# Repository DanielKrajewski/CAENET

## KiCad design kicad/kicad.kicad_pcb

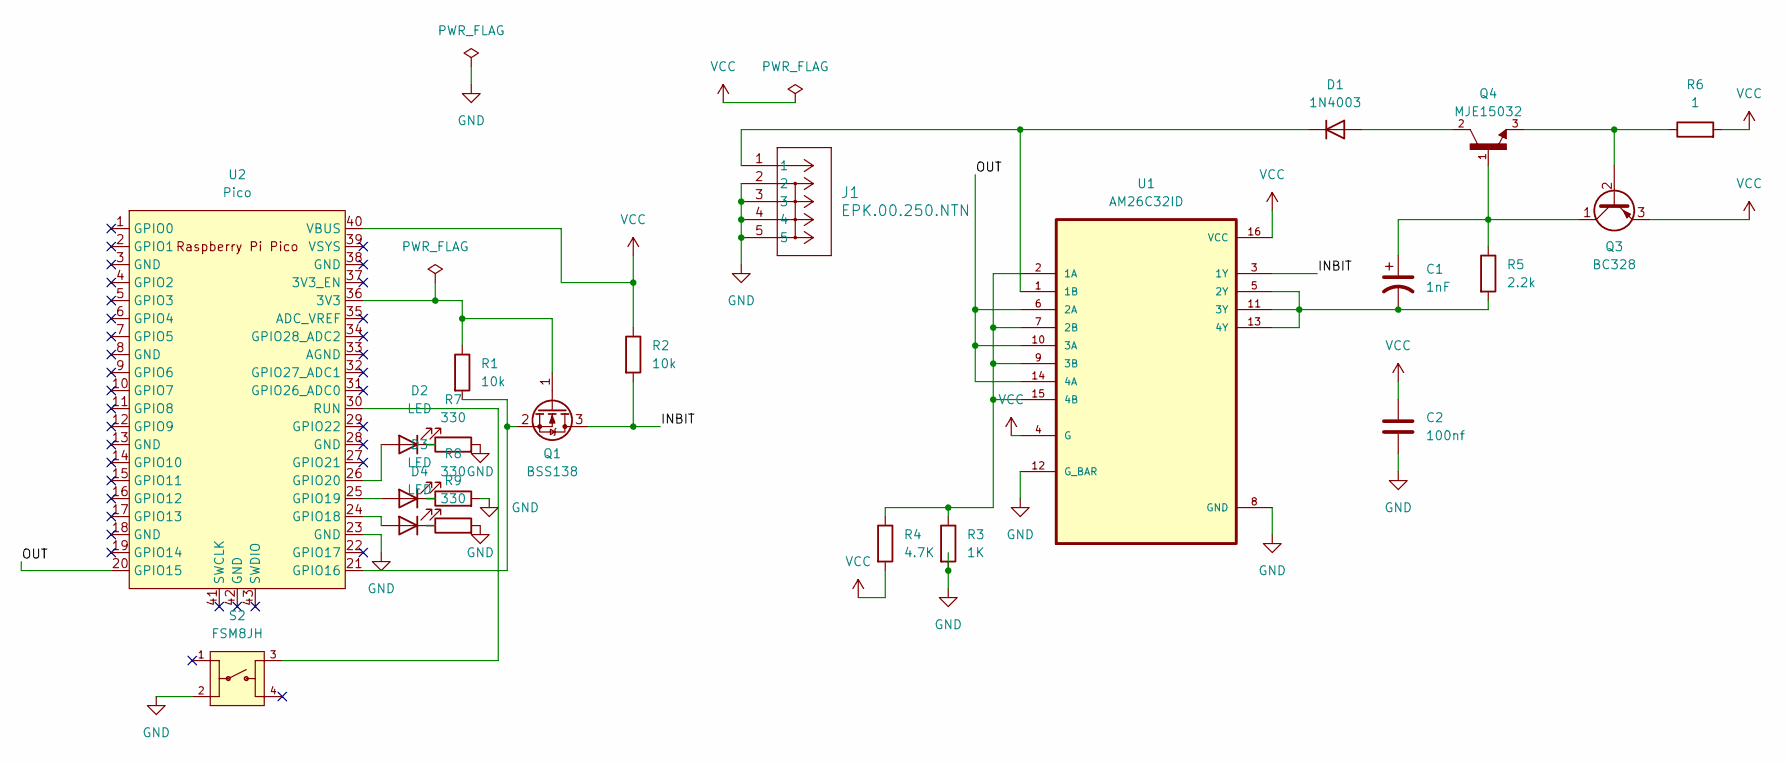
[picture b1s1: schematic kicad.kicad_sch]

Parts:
C1: 1nF; C_0603_1608Metric_Pad1.08x0.95mm_HandSolder
C2: 100nf; C_0603_1608Metric_Pad1.08x0.95mm_HandSolder
D1: 1N4003; D_DO-41_SOD81_P10.16mm_Horizontal
D2, D3, D4: LED; LED_D3.0mm
J1: EPK.00.250.NTN; CONN_EPK.00.250.NTN_LMO
Q1: BSS138; SOT-23
Q3: BC328; TO-92_Inline
Q4: MJE15032; TO-92_Inline
R1, R2: 10k; R_0603_1608Metric_Pad0.98x0.95mm_HandSolder
R3: 1K; R_0603_1608Metric_Pad0.98x0.95mm_HandSolder
R4: 4.7K; R_0603_1608Metric_Pad0.98x0.95mm_HandSolder
R5: 2.2k; R_0603_1608Metric_Pad0.98x0.95mm_HandSolder
R6: 1; R_Axial_DIN0309_L9.0mm_D3.2mm_P12.70mm_Horizontal
R7, R8, R9: 330; R_0603_1608Metric_Pad0.98x0.95mm_HandSolder
S2: FSM8JH; SW_FSM8JH; PARTREV C10
U1: AM26C32ID; SOIC127P600X175-16N
U2: Pico; RPi_Pico_SMD_TH

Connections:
/INBIT: Q1.3 (D), R2.2, U1.3 (1Y)
/OUT: U1.6 (2A), U1.10 (3A), U1.14 (4A), U2.20 (GPIO15)
GND: C2.2, J1.2, J1.3, J1.4, J1.5, R3.2, R7.2, R8.2, R9.2, S2.2, U1.8 (GND), U1.12 (G_BAR), U2.23 (GND)
unnamed: D1.2 (A), Q4.2
unnamed: D1.1 (K), J1.1, U1.1 (1B)
unnamed: D2.2 (A), U2.26 (GPIO20)
unnamed: D2.1 (K), R7.1
unnamed: D3.2 (A), U2.25 (GPIO19)
unnamed: D3.1 (K), R8.1
unnamed: D4.2 (A), U2.24 (GPIO18)
unnamed: D4.1 (K), R9.1
unnamed: Q1.1 (G), R1.1, U2.36 (3V3)
unnamed: Q1.2 (S), R1.2, U2.21 (GPIO16)
unnamed: Q3.2 (B), Q4.3, R6.1
unnamed: C1.1, Q3.1 (C), Q4.1, R5.1
unnamed: R3.1, R4.1, U1.2 (1A), U1.7 (2B), U1.9 (3B), U1.15 (4B)
unnamed: C1.2, R5.2, U1.5 (2Y), U1.11 (3Y), U1.13 (4Y)
unnamed: S2.3, U2.30 (RUN)
VCC: C2.1, Q3.3 (E), R2.1, R4.2, R6.2, U1.4 (G), U1.16 (VCC), U2.40 (VBUS)

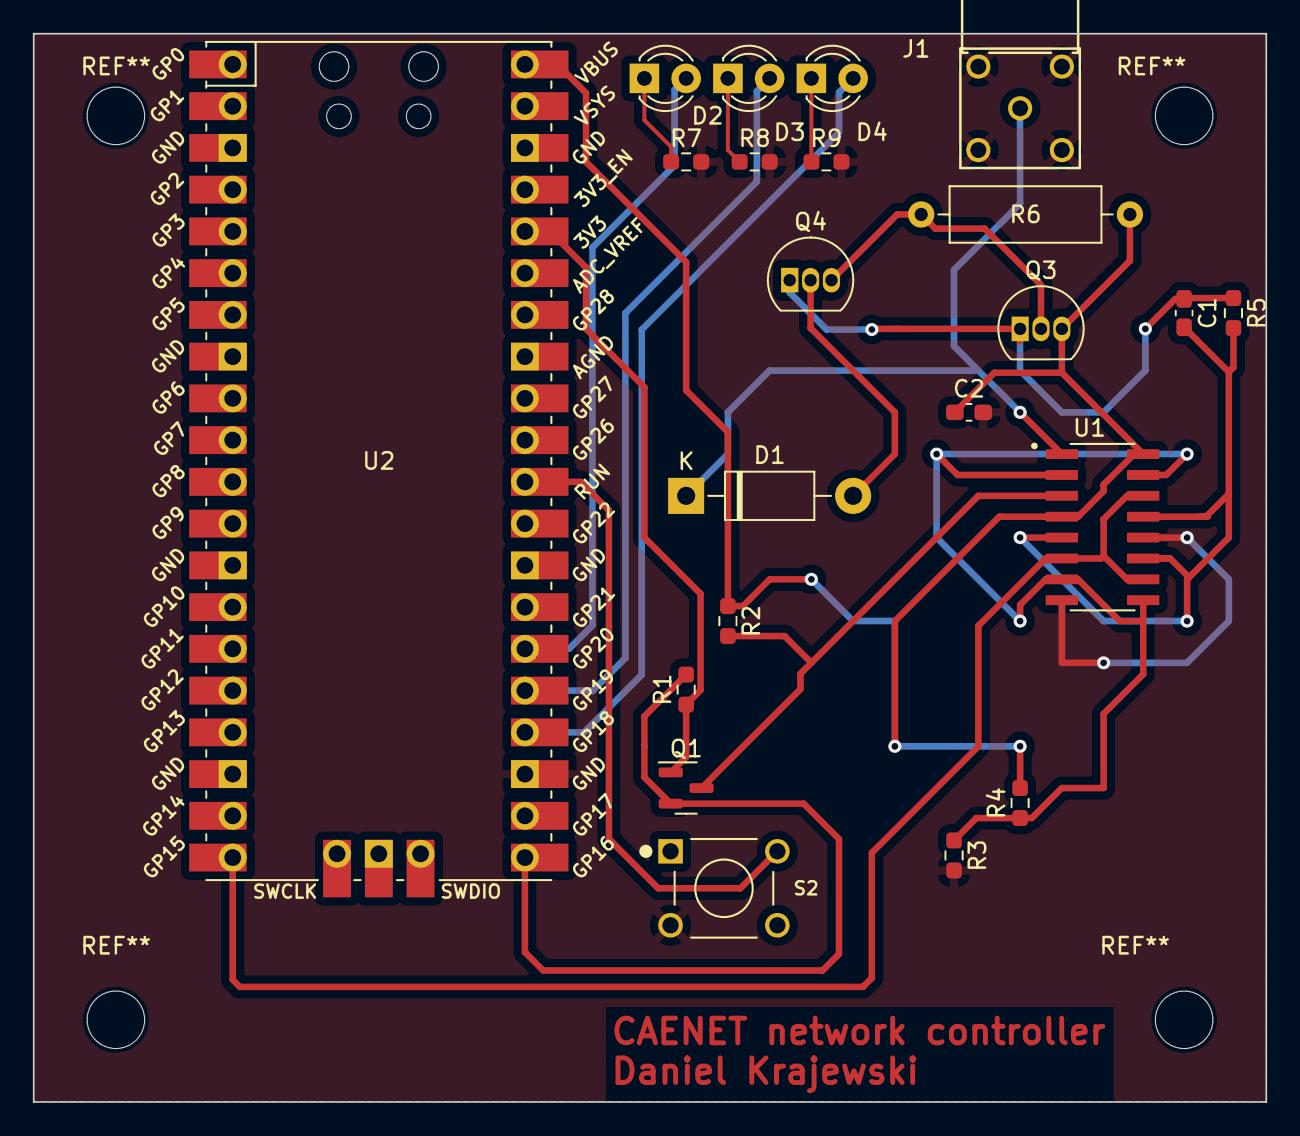
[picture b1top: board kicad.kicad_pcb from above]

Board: 2 copper layers, 75.0 x 65.0 mm, 22 parts (0 on the bottom side), 19 nets.

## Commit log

2024-01-25 Pliki
